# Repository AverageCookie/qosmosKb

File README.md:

# TKL keyboard "from scratch"

Being bored during the covid lockdown, I tried to learn a bit about electronics how my mechanical keyboard works. To practice, I wanted to build my own PCB, and why not try to build a usable keyboard.

## Disclamer : language mastery

I'm from France, I learn english mainly thanks to pop culture (TV shows/movies/videogames and lurking on reddit), so let me know if some sentences are gibberish or if I'm not clear enough.

## Table of Contents

* [Learning sources](#learning-sources)
* [Software/equipment/services used](#software-equipment-services-used)
* [Schematics](#schematics)
* [PCB](#pcb-design)
* [Soldering](#soldering)
* [Flashing Firmware](#flashing-firmware)
* [Troubles oh troubles](#troubles-oh-troubles)

## Learning sources

I learned how matrices works thanks to [r/MechanicalKeyboards/](https://www.reddit.com/r/MechanicalKeyboards/), and soon found [ruiqimao's awesome guide](https://github.com/ruiqimao/keyboard-pcb-guide). As you will see, the schematics I made are very similar to his.

## Software/equipment/services used

* For schematics and pcb design, I used [Kicad](https://kicad-pcb.org/).
* For pcb manufacturing, I went to [JLCPCB](https://jlcpcb.com/).
* For components, I went to [Digikey](https://www.digikey.com/) and [RS components](https://www.rs-online.com/)
* For soldering tools and materials, I bought from divers Amazon sellers :
    * [Soldering tools](https://www.amazon.fr/gp/product/B07PLTB46N/ref=ppx_yo_dt_b_asin_title_o06_s01?ie=UTF8&psc=1)
    * [Flux](https://www.amazon.fr/gp/product/B002OB4CIE/ref=ppx_yo_dt_b_asin_title_o05_s00)
    * [Solder](https://www.amazon.fr/gp/product/B07PDFF5NZ/ref=ppx_yo_dt_b_asin_title_o06_s01)
* For plate and case design, I used [Blender](https://www.blender.org/),
* For plate and case printing, I used my [Ender3](https://www.ender3.fr/) 3D printer.
* for switches and stabilizers, I bought from [kbdfans](https://kbdfans.com/)

## Schematics

Inspired by [u/Ryvaeus](https://www.reddit.com/r/MechanicalKeyboards/comments/4qdu9o/help_ive_planned_my_matrix_and_teensy_pinout_for/), I went for a 12*9 matrice :

I did a first try with micro USB, but had a lot of problems soldering correctly, so I made a USB B + holes (so i can have an option to solder a non removable cable) 2nd version.

## PCB Design

It was the first PCB I designed, I'm pretty proud but I guess there might be a problem as you will see right bellow. 

## Soldering

I have not soldered diodes for now because of the issues you will learn about in the next chapter.

## Flashing Firmware

I plugged it into my desktop, pressed the RESET button, and flashed it with QMK Toolbox (there was no error). But then nothing, so I unplugged and replugged it, to have windows tel me "USB descriptor failed".

## Troubles oh troubles

I tried to re-install my USB controllers driver, I tried to flash a few more time, even changing from QMK toolbox to QMK flasher, but I could not make it work.

Then I tried to plug it on my laptop (XPS13, with USB C adaptator), and it was recognised as the keyboard it is destined to be !

Thinking the USB Male port could be the problem, I replaced the cable by one I know works perfectly. It was unproductive, and strangely it does not work anymore on my laptop (same errors as in my desktop) I tried again to re-install my USB controllers driver on both machines, nothing.

I tried to discharge capacitors before plugging it in, and it seems to connect and disconnect maybe 5 times before showing me the "USB descriptor failed" error.

I just tried to get into DFU mode by using the RESET button, and it does not even work..

You can find all the sources (except the v1 schematics, I cannot find it, I think I threw it) in the repo.

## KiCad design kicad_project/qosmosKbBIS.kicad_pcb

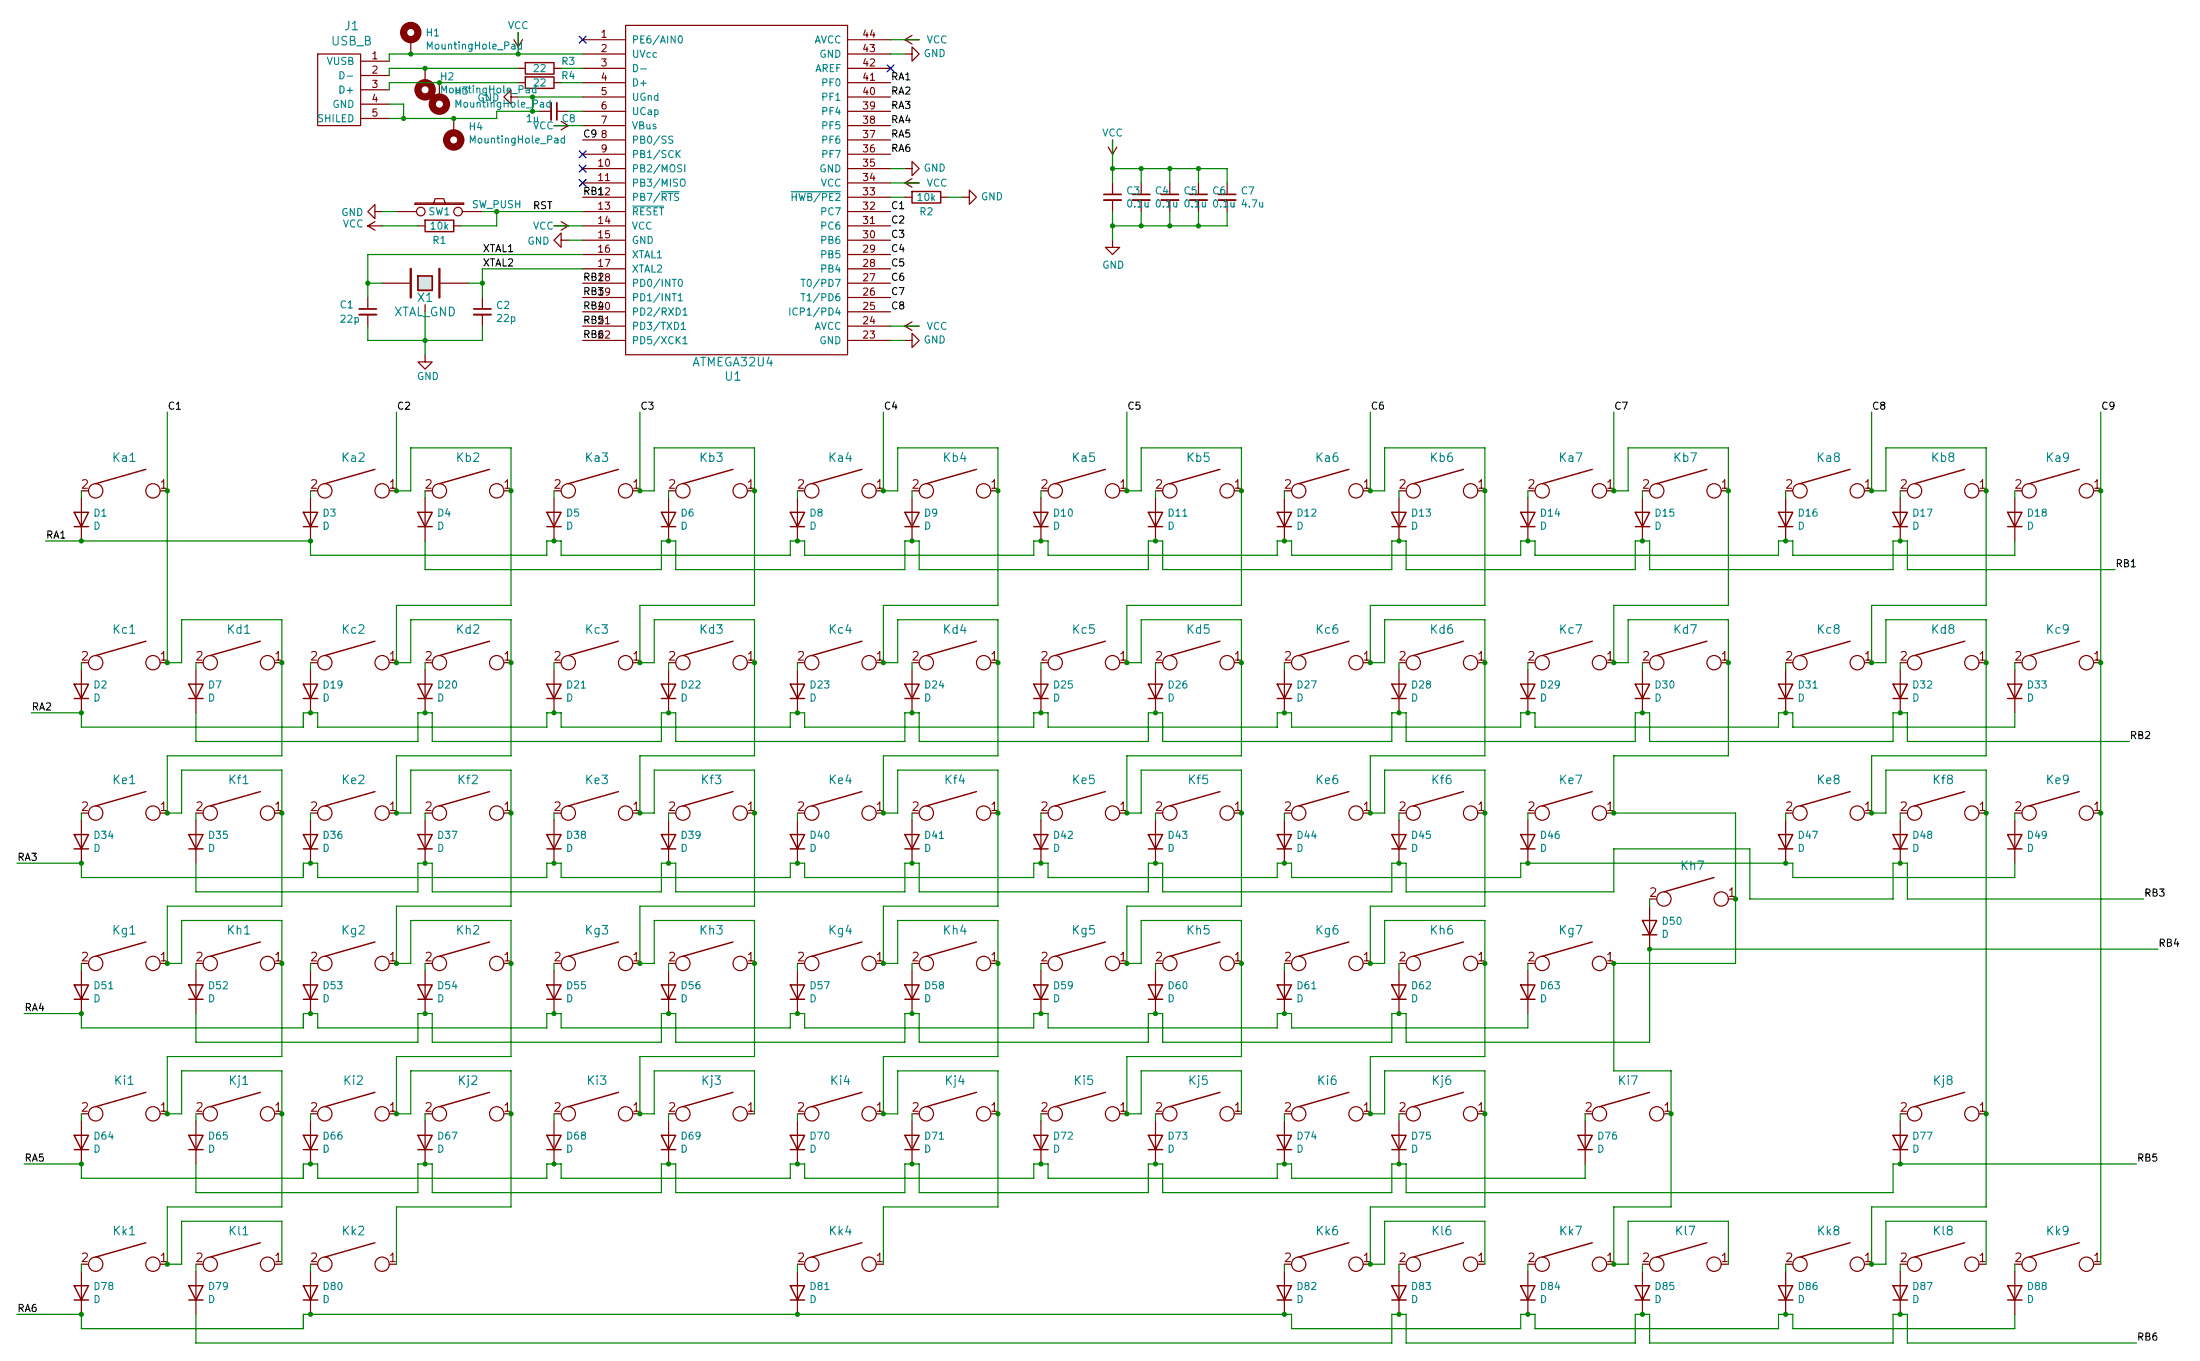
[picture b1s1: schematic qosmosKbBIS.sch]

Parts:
C1, C2: 22p; C_0805_2012Metric_Pad1.15x1.40mm_HandSolder
C3, C4, C5, C6: 0.1u; C_0805_2012Metric_Pad1.15x1.40mm_HandSolder
C7: 4.7u; C_0805_2012Metric_Pad1.15x1.40mm_HandSolder
C8: 1u; C_0805_2012Metric_Pad1.15x1.40mm_HandSolder
D1, D2, D3, D4, D5, D6, D7, D8, D9, D10, D11, D12, D13, D14, D15, D16, D17, D18, D19, D20, D21, D22, D23, D24, D25, D26, D27, D28, D29, D30, D31, D32, D33, D34, D35, D36, D37, D38, D39, D40, D41, D42, D43, D44, D45, D46, D47, D48, D49, D50, D51, D52, D53, D54, D55, D56, D57, D58, D59, D60, D61, D62, D63, D64, D65, D66, D67, D68, D69, D70, D71, D72, D73, D74, D75, D76, D77, D78, D79, D80, D81, D82, D83, D84, D85, D86, D87, D88: D; D_SOD123_axial
H1, H2, H3, H4: MountingHole_Pad; MountingHole_2.2mm_M2_ISO14580_Pad
J1: USB_B; USB_B_OST_USB-B1HSxx_Horizontal
Ka1, Ka2, Ka3, Ka4, Ka5, Ka6, Ka7, Ka8, Ka9: KEYSW; SW_Cherry_MX_1.00u_PCB
Kb2, Kb3, Kb4, Kb5, Kb6, Kb7, Kb8: KEYSW; SW_Cherry_MX_1.00u_PCB
Kc1, Kc2, Kc3, Kc4, Kc5, Kc6, Kc7, Kc8, Kc9: KEYSW; SW_Cherry_MX_1.00u_PCB
Kd1, Kd2, Kd3, Kd4, Kd5, Kd6, Kd8: KEYSW; SW_Cherry_MX_1.00u_PCB
Kd7: KEYSW; SW_Cherry_MX_2.00u_PCB
Ke1: KEYSW; SW_Cherry_MX_1.50u_PCB
Ke2, Ke3, Ke4, Ke5, Ke6, Ke7, Ke8, Ke9: KEYSW; SW_Cherry_MX_1.00u_PCB
Kf1, Kf2, Kf3, Kf4, Kf5, Kf6, Kf8: KEYSW; SW_Cherry_MX_1.00u_PCB
Kg1: KEYSW; SW_Cherry_MX_1.75u_PCB
Kg2, Kg3, Kg4, Kg5, Kg6, Kg7: KEYSW; SW_Cherry_MX_1.00u_PCB
Kh1, Kh2, Kh3, Kh4, Kh5, Kh6: KEYSW; SW_Cherry_MX_1.00u_PCB
Kh7: KEYSW; SW_Cherry_MX_ISOEnter_PCB
Ki1: KEYSW; SW_Cherry_MX_1.25u_PCB
Ki2, Ki3, Ki4, Ki5, Ki6: KEYSW; SW_Cherry_MX_1.00u_PCB
Ki7: KEYSW; SW_Cherry_MX_2.75u_PCB
Kj1, Kj2, Kj3, Kj4, Kj5, Kj6, Kj8: KEYSW; SW_Cherry_MX_1.00u_PCB
Kk1, Kk2, Kk6, Kk7: KEYSW; SW_Cherry_MX_1.25u_PCB
Kk4: KEYSW; SW_Cherry_MX_6.25u_PCB
Kk8, Kk9: KEYSW; SW_Cherry_MX_1.00u_PCB
Kl1, Kl6, Kl7: KEYSW; SW_Cherry_MX_1.25u_PCB
Kl8: KEYSW; SW_Cherry_MX_1.00u_PCB
R1, R2: 10k; R_0805_2012Metric_Pad1.15x1.40mm_HandSolder
R3, R4: 22; R_0805_2012Metric_Pad1.15x1.40mm_HandSolder
SW1: SW_PUSH; SW_SPST_TL3342
U1: ATMEGA32U4; TQFP-44_10x10mm_P0.8mm
X1: XTAL_GND; FA-238

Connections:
/C1: Ka1.1, Kc1.1, Kd1.1, Ke1.1, Kf1.1, Kg1.1, Kh1.1, Ki1.1, Kj1.1, Kk1.1, Kl1.1, U1.32 (PC7)
/C2: Ka2.1, Kb2.1, Kc2.1, Kd2.1, Ke2.1, Kf2.1, Kg2.1, Kh2.1, Ki2.1, Kj2.1, Kk2.1, U1.31 (PC6)
/C3: Ka3.1, Kb3.1, Kc3.1, Kd3.1, Ke3.1, Kf3.1, Kg3.1, Kh3.1, Ki3.1, Kj3.1, U1.30 (PB6)
/C4: Ka4.1, Kb4.1, Kc4.1, Kd4.1, Ke4.1, Kf4.1, Kg4.1, Kh4.1, Ki4.1, Kj4.1, Kk4.1, U1.29 (PB5)
/C5: Ka5.1, Kb5.1, Kc5.1, Kd5.1, Ke5.1, Kf5.1, Kg5.1, Kh5.1, Ki5.1, Kj5.1, U1.28 (PB4)
/C6: Ka6.1, Kb6.1, Kc6.1, Kd6.1, Ke6.1, Kf6.1, Kg6.1, Kh6.1, Ki6.1, Kj6.1, Kk6.1, Kl6.1, U1.27 (T0/PD7)
/C7: Ka7.1, Kb7.1, Kc7.1, Kd7.1, Ke7.1, Kg7.1, Kh7.1, Ki7.1, Kk7.1, Kl7.1, U1.26 (T1/PD6)
/C8: Ka8.1, Kb8.1, Kc8.1, Kd8.1, Ke8.1, Kf8.1, Kj8.1, Kk8.1, Kl8.1, U1.25 (ICP1/PD4)
/C9: Ka9.1, Kc9.1, Ke9.1, Kk9.1, U1.8 (PB0/SS)
/RA1: D1.1 (K), D3.1 (K), D5.1 (K), D8.1 (K), D10.1 (K), D12.1 (K), D14.1 (K), D16.1 (K), D18.1 (K), U1.41 (PF0)
/RA2: D2.1 (K), D19.1 (K), D21.1 (K), D23.1 (K), D25.1 (K), D27.1 (K), D29.1 (K), D31.1 (K), D33.1 (K), U1.40 (PF1)
/RA3: D34.1 (K), D36.1 (K), D38.1 (K), D40.1 (K), D42.1 (K), D44.1 (K), D46.1 (K), D47.1 (K), D49.1 (K), U1.39 (PF4)
/RA4: D51.1 (K), D53.1 (K), D55.1 (K), D57.1 (K), D59.1 (K), D61.1 (K), D63.1 (K), U1.38 (PF5)
/RA5: D64.1 (K), D66.1 (K), D68.1 (K), D70.1 (K), D72.1 (K), D74.1 (K), D76.1 (K), U1.37 (PF6)
/RA6: D78.1 (K), D80.1 (K), D81.1 (K), D82.1 (K), D84.1 (K), D86.1 (K), D88.1 (K), U1.36 (PF7)
/RB1: D4.1 (K), D6.1 (K), D9.1 (K), D11.1 (K), D13.1 (K), D15.1 (K), D17.1 (K), U1.12 (PB7/~RTS)
/RB2: D7.1 (K), D20.1 (K), D22.1 (K), D24.1 (K), D26.1 (K), D28.1 (K), D30.1 (K), D32.1 (K), U1.18 (PD0/INT0)
/RB3: D35.1 (K), D37.1 (K), D39.1 (K), D41.1 (K), D43.1 (K), D45.1 (K), D48.1 (K), U1.19 (PD1/INT1)
/RB4: D50.1 (K), D52.1 (K), D54.1 (K), D56.1 (K), D58.1 (K), D60.1 (K), D62.1 (K), U1.20 (PD2/RXD1)
/RB5: D65.1 (K), D67.1 (K), D69.1 (K), D71.1 (K), D73.1 (K), D75.1 (K), D77.1 (K), U1.21 (PD3/TXD1)
/RB6: D79.1 (K), D83.1 (K), D85.1 (K), D87.1 (K), U1.22 (PD5/XCK1)
/RST: R1.1, SW1.2, U1.13 (~RESET)
/XTAL1: C1.1, U1.16 (XTAL1), X1.1
/XTAL2: C2.1, U1.17 (XTAL2), X1.2
GND: C1.2, C2.2, C3.2, C4.2, C5.2, C6.2, C7.2, C8.2, H4.1, J1.4 (GND), J1.5 (SHILED), R2.1, SW1.1, U1.5 (UGnd), U1.15 (GND), U1.23 (GND), U1.35 (GND), U1.43 (GND), X1.3
unnamed: C8.1, U1.6 (UCap)
unnamed: D1.2 (A), Ka1.2
unnamed: D2.2 (A), Kc1.2
unnamed: D3.2 (A), Ka2.2
unnamed: D4.2 (A), Kb2.2
unnamed: D5.2 (A), Ka3.2
unnamed: D6.2 (A), Kb3.2
unnamed: D7.2 (A), Kd1.2
unnamed: D8.2 (A), Ka4.2
unnamed: D9.2 (A), Kb4.2
unnamed: D10.2 (A), Ka5.2
unnamed: D11.2 (A), Kb5.2
unnamed: D12.2 (A), Ka6.2
unnamed: D13.2 (A), Kb6.2
unnamed: D14.2 (A), Ka7.2
unnamed: D15.2 (A), Kb7.2
unnamed: D16.2 (A), Ka8.2
unnamed: D17.2 (A), Kb8.2
unnamed: D18.2 (A), Ka9.2
unnamed: D19.2 (A), Kc2.2
unnamed: D20.2 (A), Kd2.2
unnamed: D21.2 (A), Kc3.2
unnamed: D22.2 (A), Kd3.2
unnamed: D23.2 (A), Kc4.2
unnamed: D24.2 (A), Kd4.2
unnamed: D25.2 (A), Kc5.2
unnamed: D26.2 (A), Kd5.2
unnamed: D27.2 (A), Kc6.2
unnamed: D28.2 (A), Kd6.2
unnamed: D29.2 (A), Kc7.2
unnamed: D30.2 (A), Kd7.2
unnamed: D31.2 (A), Kc8.2
unnamed: D32.2 (A), Kd8.2
unnamed: D33.2 (A), Kc9.2
unnamed: D34.2 (A), Ke1.2
unnamed: D35.2 (A), Kf1.2
unnamed: D36.2 (A), Ke2.2
unnamed: D37.2 (A), Kf2.2
unnamed: D38.2 (A), Ke3.2
unnamed: D39.2 (A), Kf3.2
unnamed: D40.2 (A), Ke4.2
unnamed: D41.2 (A), Kf4.2
unnamed: D42.2 (A), Ke5.2
unnamed: D43.2 (A), Kf5.2
unnamed: D44.2 (A), Ke6.2
unnamed: D45.2 (A), Kf6.2
unnamed: D46.2 (A), Ke7.2
unnamed: D47.2 (A), Ke8.2
unnamed: D48.2 (A), Kf8.2
unnamed: D49.2 (A), Ke9.2
unnamed: D50.2 (A), Kh7.2
unnamed: D51.2 (A), Kg1.2
unnamed: D52.2 (A), Kh1.2
unnamed: D53.2 (A), Kg2.2
unnamed: D54.2 (A), Kh2.2
unnamed: D55.2 (A), Kg3.2
unnamed: D56.2 (A), Kh3.2
unnamed: D57.2 (A), Kg4.2
unnamed: D58.2 (A), Kh4.2
unnamed: D59.2 (A), Kg5.2
unnamed: D60.2 (A), Kh5.2
unnamed: D61.2 (A), Kg6.2
unnamed: D62.2 (A), Kh6.2
unnamed: D63.2 (A), Kg7.2
unnamed: D64.2 (A), Ki1.2
unnamed: D65.2 (A), Kj1.2
unnamed: D66.2 (A), Ki2.2
unnamed: D67.2 (A), Kj2.2
unnamed: D68.2 (A), Ki3.2
unnamed: D69.2 (A), Kj3.2
unnamed: D70.2 (A), Ki4.2
unnamed: D71.2 (A), Kj4.2
unnamed: D72.2 (A), Ki5.2
unnamed: D73.2 (A), Kj5.2
unnamed: D74.2 (A), Ki6.2
unnamed: D75.2 (A), Kj6.2
unnamed: D76.2 (A), Ki7.2
unnamed: D77.2 (A), Kj8.2
unnamed: D78.2 (A), Kk1.2
unnamed: D79.2 (A), Kl1.2
unnamed: D80.2 (A), Kk2.2
unnamed: D81.2 (A), Kk4.2
unnamed: D82.2 (A), Kk6.2
unnamed: D83.2 (A), Kl6.2
unnamed: D84.2 (A), Kk7.2
unnamed: D85.2 (A), Kl7.2
unnamed: D86.2 (A), Kk8.2
unnamed: D87.2 (A), Kl8.2
unnamed: D88.2 (A), Kk9.2
unnamed: H2.1, J1.2 (D-), R3.2
unnamed: H3.1, J1.3 (D+), R4.2
unnamed: R2.2, U1.33 (~HWB/PE2)
unnamed: R3.1, U1.3 (D-)
unnamed: R4.1, U1.4 (D+)
VCC: C3.1, C4.1, C5.1, C6.1, C7.1, H1.1, J1.1 (VUSB), R1.2, U1.2 (UVcc), U1.7 (VBus), U1.14 (VCC), U1.24 (AVCC), U1.34 (VCC), U1.44 (AVCC)

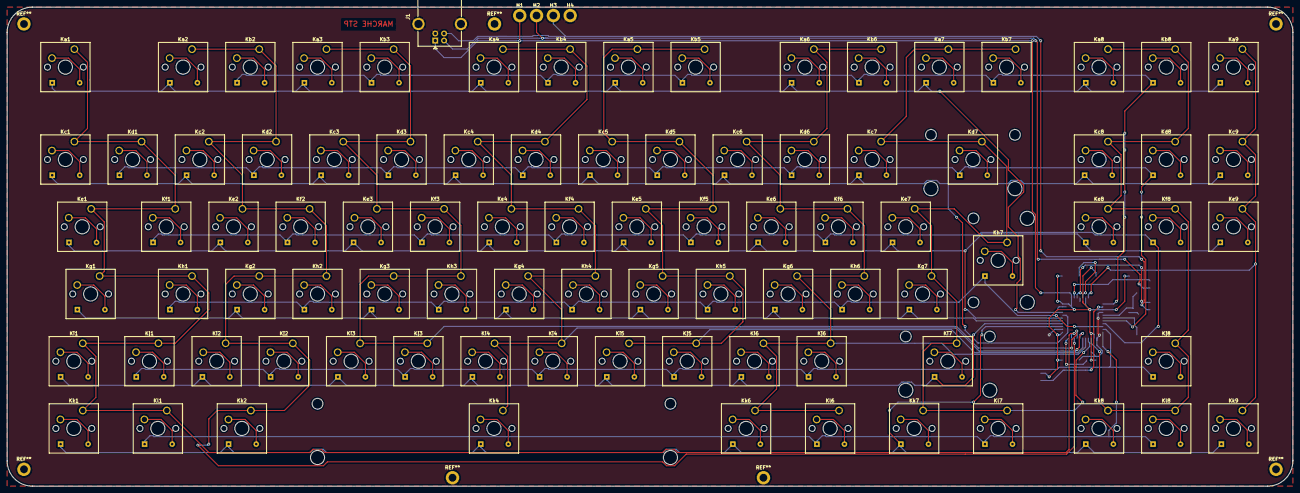
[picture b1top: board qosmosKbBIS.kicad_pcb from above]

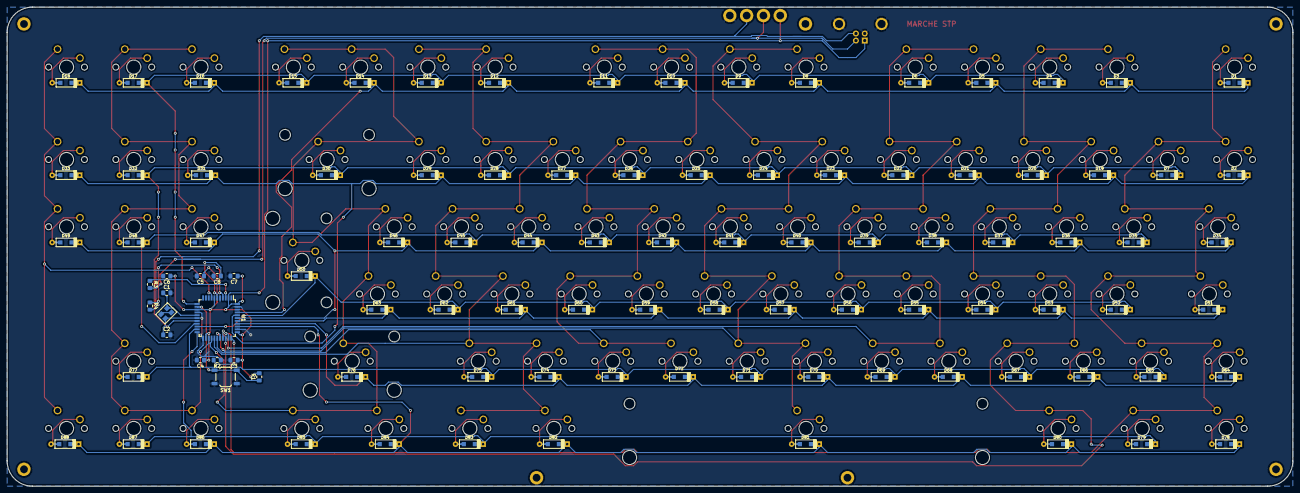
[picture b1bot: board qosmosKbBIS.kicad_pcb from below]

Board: 2 copper layers, 364.3 x 135.7 mm, 196 parts (103 on the bottom side), 120 nets.

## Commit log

2020-08-22 :space_invader: Added .gitattributes & .gitignore files
2020-08-22 Readme and sources
2020-08-22 change pictures format
2020-08-22 change img name
2020-08-22 List design
